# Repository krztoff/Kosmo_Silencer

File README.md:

# Kosmo_Silencer
Kosmo adaptation of the Befaco DivKid Mutes module

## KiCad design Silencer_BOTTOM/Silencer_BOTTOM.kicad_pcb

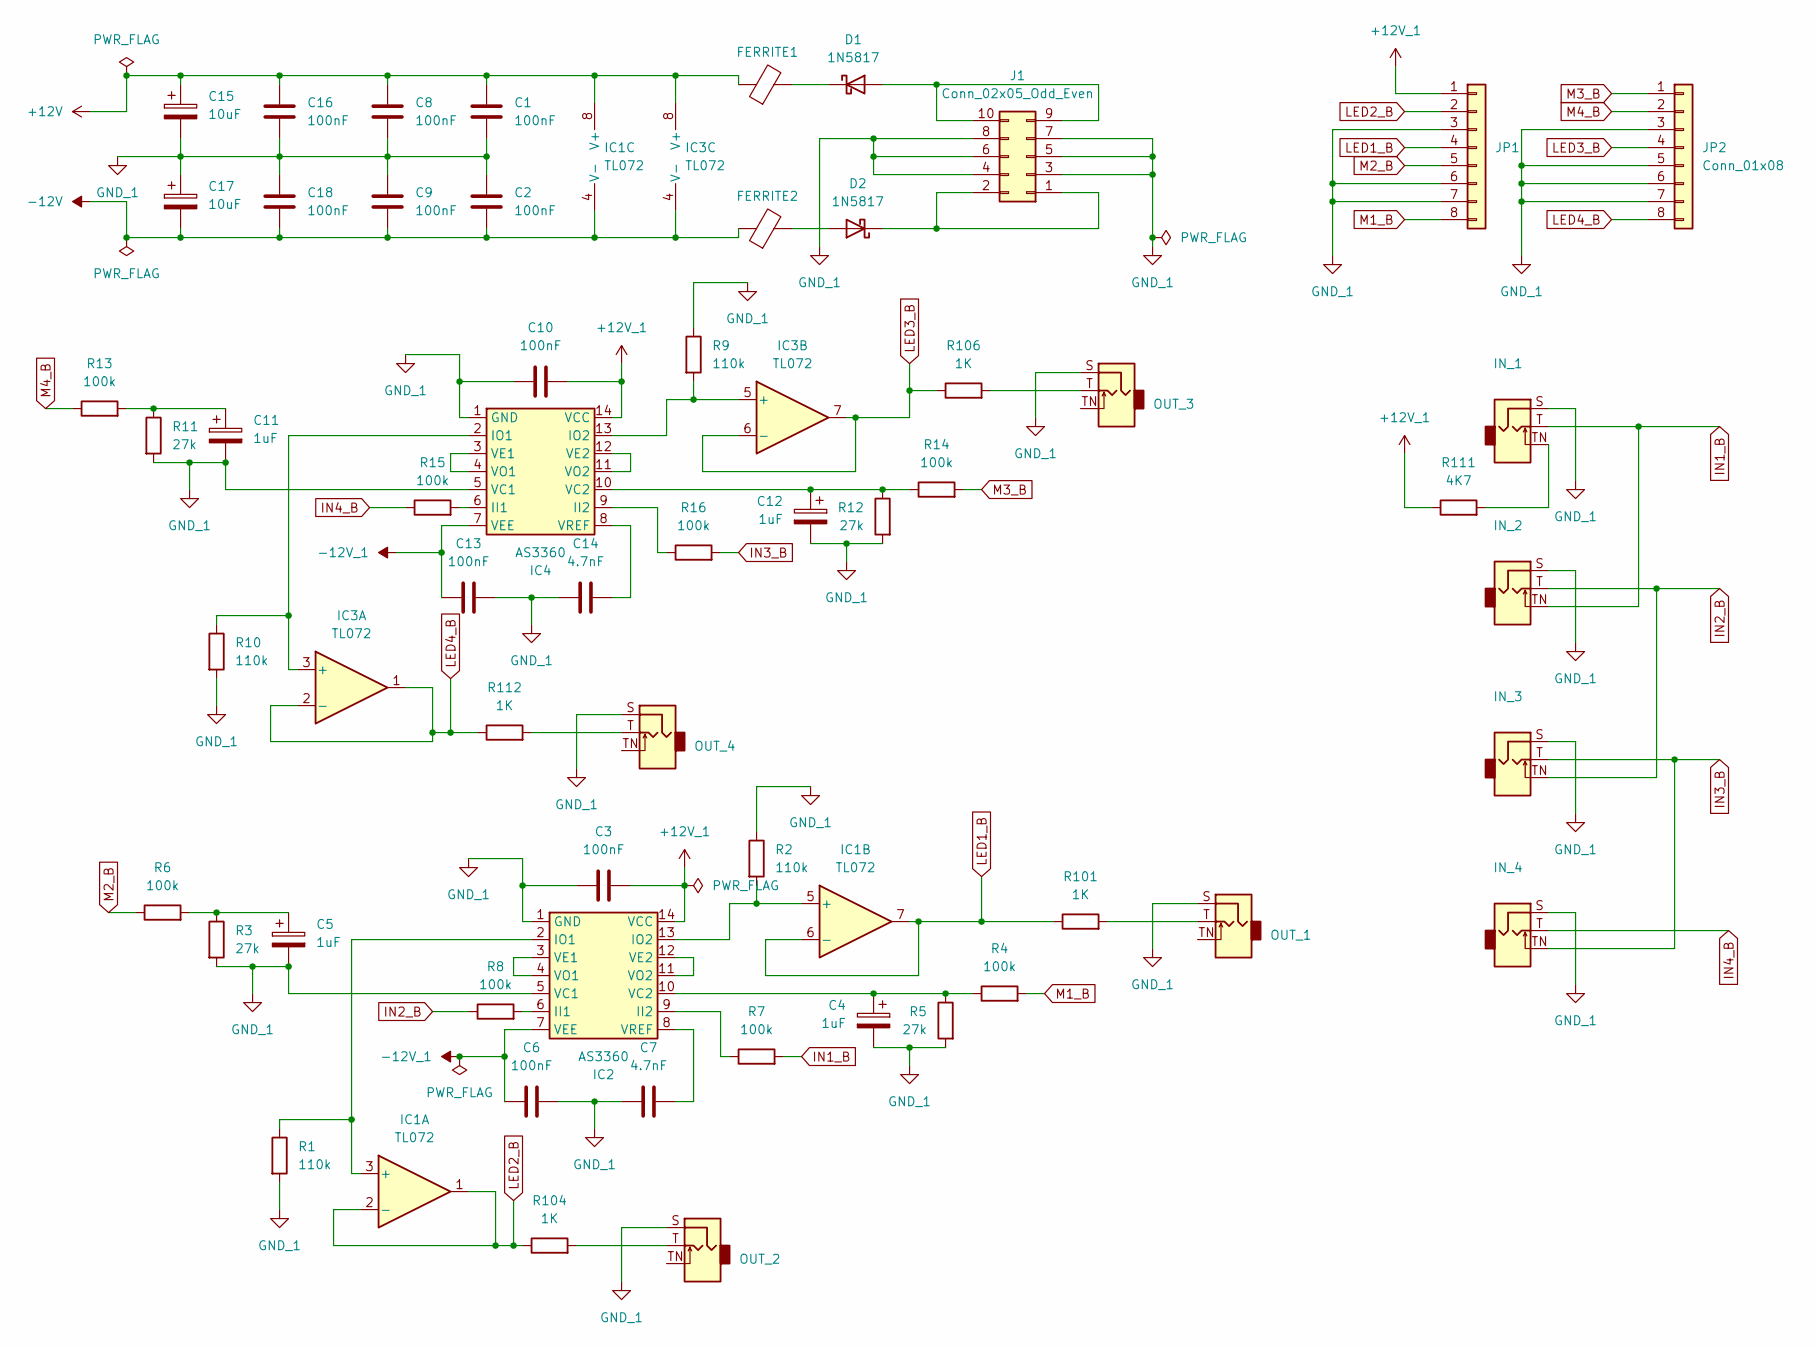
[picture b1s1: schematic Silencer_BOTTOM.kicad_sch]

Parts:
C1, C2, C3, C6, C8, C9, C10, C13, C16, C18: 100nF; C_Disc_D3.0mm_W2.0mm_P2.50mm
C4, C5, C11, C12: 1uF; CP_Radial_D6.3mm_P2.50mm
C7, C14: 4.7nF; C_Disc_D3.0mm_W2.0mm_P2.50mm
C15, C17: 10uF; CP_Radial_D6.3mm_P2.50mm
D1, D2: 1N5817; D_DO-41_SOD81_P10.16mm_Horizontal
FERRITE1, FERRITE2: FerriteBead; R_Axial_DIN0207_L6.3mm_D2.5mm_P10.16mm_Horizontal
IC1, IC3: TL072; DIP-8_W7.62mm_Socket_LongPads
IC2, IC4: AS3360; DIP-14_W7.62mm_LongPads
IN_1, IN_2, IN_3, IN_4: AudioJack2_SwitchT; Jack_6.35mm_PJ_629HAN_slots
J1: Conn_02x05_Odd_Even; Power_Header
JP1, JP2: Conn_01x08; PinHeader_1x08_P2.54mm_Vertical
OUT_1, OUT_2, OUT_3, OUT_4: AudioJack2_SwitchT; Jack_6.35mm_PJ_629HAN_slots
R1, R2, R9, R10: 110k; R_Axial_DIN0207_L6.3mm_D2.5mm_P10.16mm_Horizontal
R3, R5, R11, R12: 27k; R_Axial_DIN0207_L6.3mm_D2.5mm_P10.16mm_Horizontal
R4, R6, R7, R8, R13, R14, R15, R16: 100k; R_Axial_DIN0207_L6.3mm_D2.5mm_P10.16mm_Horizontal
R101, R104, R106, R112: 1K; R_Axial_DIN0207_L6.3mm_D2.5mm_P10.16mm_Horizontal
R111: 4K7; R_Axial_DIN0207_L6.3mm_D2.5mm_P10.16mm_Horizontal

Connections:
+12V: C1.1, C8.1, C15.1, C16.1, FERRITE1.1, IC1.8 (V+), IC3.8 (V+)
+12V_1: C3.2, C10.2, IC2.14 (VCC), IC4.14 (VCC), JP1.1, R111.1
-12V: C2.2, C9.2, C17.2, C18.2, FERRITE2.1, IC1.4 (V-), IC3.4 (V-)
-12V_1: C6.1, C13.1, IC2.7 (VEE), IC4.7 (VEE)
GND_1: C1.2, C2.1, C3.1, C4.2, C5.2, C6.2, C7.1, C8.2, C9.1, C10.1, C11.2, C12.2, C13.2, C14.1, C15.2, C16.2, C17.1, C18.1, IC2.1 (GND), IC2.5 (VC1), IC4.1 (GND), IC4.5 (VC1), IN_1.S, IN_2.S, IN_3.S, IN_4.S, J1.3, J1.4, J1.5, J1.6, J1.7, J1.8, JP1.3, JP1.6, JP1.7, JP2.3, JP2.5, JP2.6, JP2.7, OUT_1.S, OUT_2.S, OUT_3.S, OUT_4.S, R1.2, R2.1, R3.2, R5.2, R9.1, R10.2, R11.2, R12.2
IN1_B: IN_1.T, IN_2.TN, R7.2
IN2_B: IN_2.T, IN_3.TN, R8.1
IN3_B: IN_3.T, IN_4.TN, R16.2
IN4_B: IN_4.T, R15.1
LED1_B: IC1.6 (-), IC1.7, JP1.4, R101.1
LED2_B: IC1.1, IC1.2 (-), JP1.2, R104.1
LED3_B: IC3.6 (-), IC3.7, JP2.4, R106.1
LED4_B: IC3.1, IC3.2 (-), JP2.8, R112.1
M1_B: JP1.8, R4.2
M2_B: JP1.5, R6.1
M3_B: JP2.1, R14.2
M4_B: JP2.2, R13.1
unnamed: C5.1, R3.1, R6.2
unnamed: C11.1, R11.1, R13.2
unnamed: D1.2 (A), J1.9, J1.10
unnamed: D1.1 (K), FERRITE1.2
unnamed: D2.2 (A), FERRITE2.2
unnamed: D2.1 (K), J1.1, J1.2
unnamed: IC1.3 (+), IC2.2 (IO1), R1.1
unnamed: IC1.5 (+), IC2.13 (IO2), R2.2
unnamed: IC2.6 (II1), R8.2
unnamed: IC2.9 (II2), R7.1
unnamed: C4.1, IC2.10 (VC2), R4.1, R5.1
unnamed: IC2.3 (VE1), IC2.4 (VO1)
unnamed: IC2.11 (VO2), IC2.12 (VE2)
unnamed: C7.2, IC2.8 (VREF)
unnamed: IC3.3 (+), IC4.2 (IO1), R10.1
unnamed: IC3.5 (+), IC4.13 (IO2), R9.2
unnamed: IC4.6 (II1), R15.2
unnamed: IC4.9 (II2), R16.1
unnamed: C12.1, IC4.10 (VC2), R12.1, R14.1
unnamed: IC4.3 (VE1), IC4.4 (VO1)
unnamed: IC4.11 (VO2), IC4.12 (VE2)
unnamed: C14.2, IC4.8 (VREF)
unnamed: IN_1.TN, R111.2
unnamed: OUT_1.T, R101.2
unnamed: OUT_2.T, R104.2
unnamed: OUT_3.T, R106.2
unnamed: OUT_4.T, R112.2

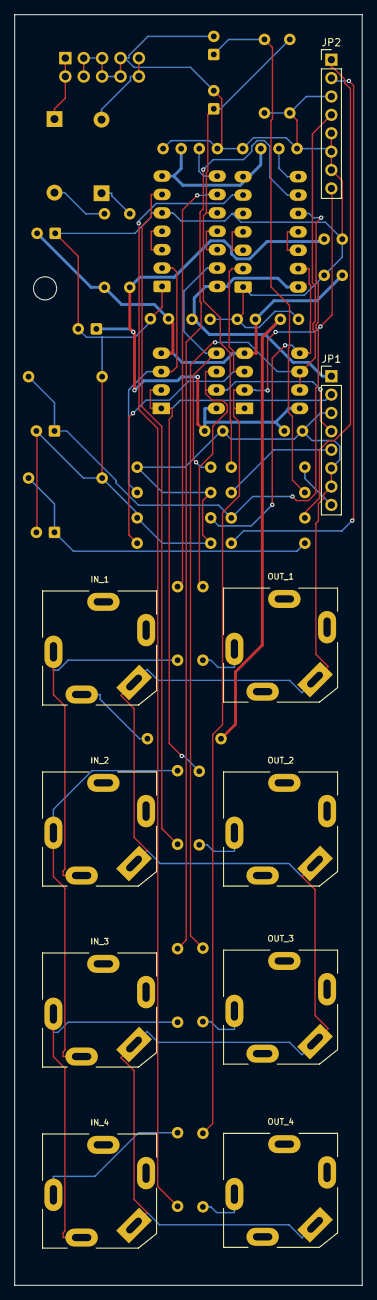
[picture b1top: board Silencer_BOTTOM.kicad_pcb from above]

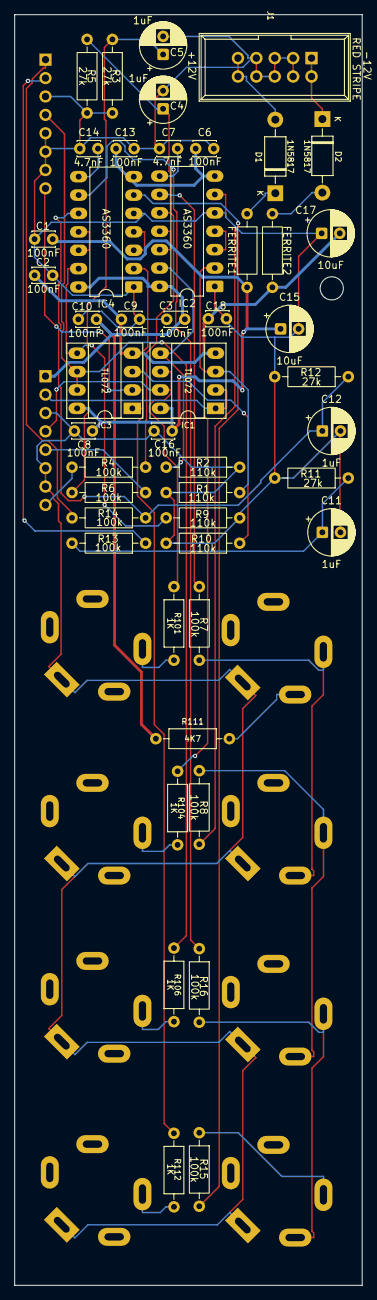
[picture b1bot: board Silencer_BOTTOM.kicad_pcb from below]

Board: 2 copper layers, 48.0 x 175.5 mm, 58 parts (48 on the bottom side), 44 nets.

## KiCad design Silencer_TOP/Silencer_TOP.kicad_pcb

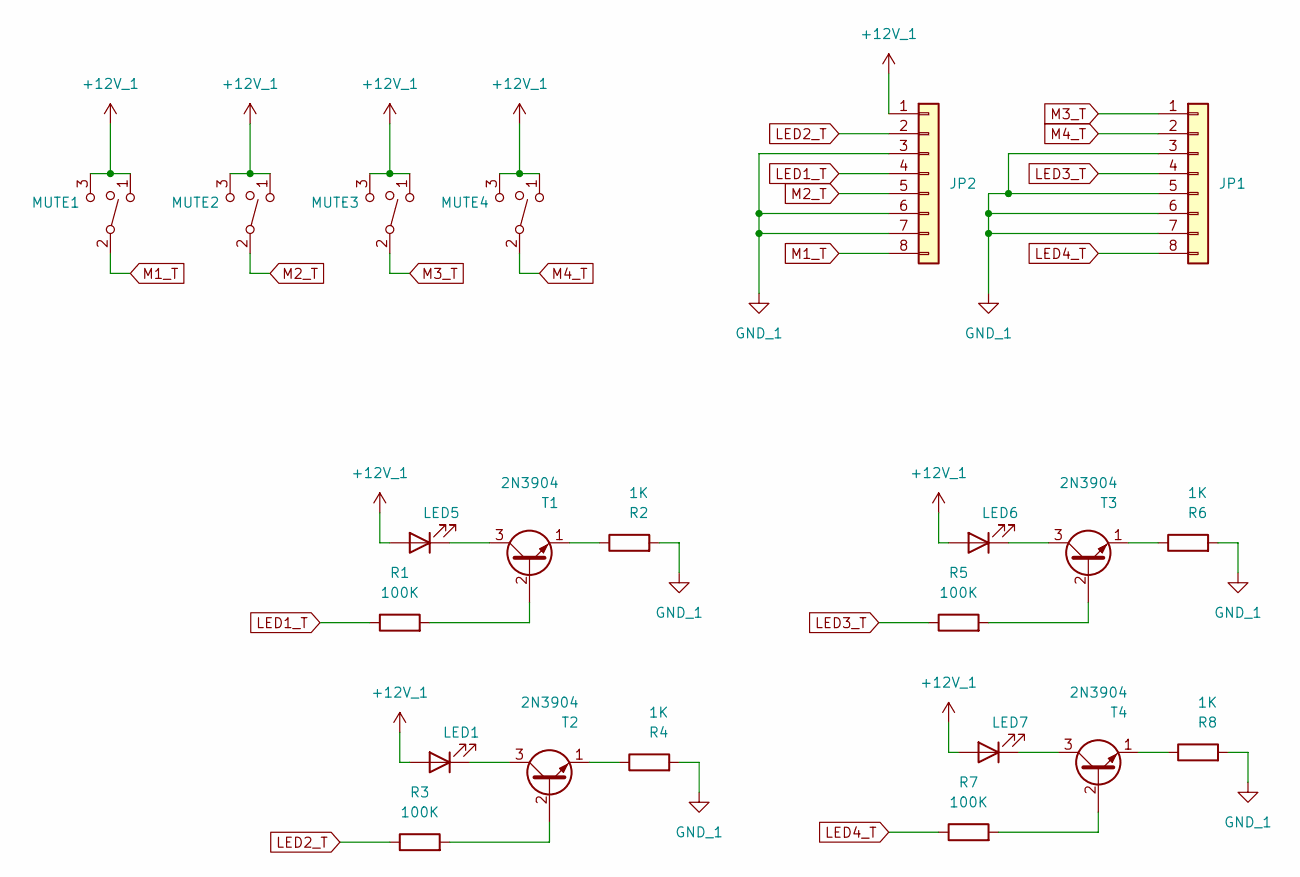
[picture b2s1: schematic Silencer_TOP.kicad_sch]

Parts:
JP1, JP2: Conn_01x08_MountingPin; PinHeader_1x08_P2.54mm_Vertical
LED1, LED5, LED6, LED7: LED_red; LED_D5.0mm
MUTE1, MUTE2, MUTE3, MUTE4: SW_SPDT_MSM; SPDT-toggle-switch-1M-series
R1, R3, R5, R7: 100K; R_Axial_DIN0207_L6.3mm_D2.5mm_P10.16mm_Horizontal
R2, R4, R6, R8: 1K; R_Axial_DIN0207_L6.3mm_D2.5mm_P10.16mm_Horizontal
T1, T2, T3, T4: 2N3904; TO-92_Inline_Wide

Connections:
+12V_1: JP2.1, LED1.2 (A), LED5.2 (A), LED6.2 (A), LED7.2 (A), MUTE1.1, MUTE1.3, MUTE2.1, MUTE2.3, MUTE3.1, MUTE3.3, MUTE4.1, MUTE4.3
GND_1: JP1.3, JP1.5, JP1.6, JP1.7, JP2.3, JP2.6, JP2.7, R2.2, R4.2, R6.2, R8.2
LED1_T: JP2.4, R1.1
LED2_T: JP2.2, R3.1
LED3_T: JP1.4, R5.1
LED4_T: JP1.8, R7.1
M1_T: JP2.8, MUTE1.2
M2_T: JP2.5, MUTE2.2
M3_T: JP1.1, MUTE3.2
M4_T: JP1.2, MUTE4.2
unnamed: LED1.1 (K), T2.3 (C)
unnamed: LED5.1 (K), T1.3 (C)
unnamed: LED6.1 (K), T3.3 (C)
unnamed: LED7.1 (K), T4.3 (C)
unnamed: R1.2, T1.2 (B)
unnamed: R2.1, T1.1 (E)
unnamed: R3.2, T2.2 (B)
unnamed: R4.1, T2.1 (E)
unnamed: R5.2, T3.2 (B)
unnamed: R6.1, T3.1 (E)
unnamed: R7.2, T4.2 (B)
unnamed: R8.1, T4.1 (E)

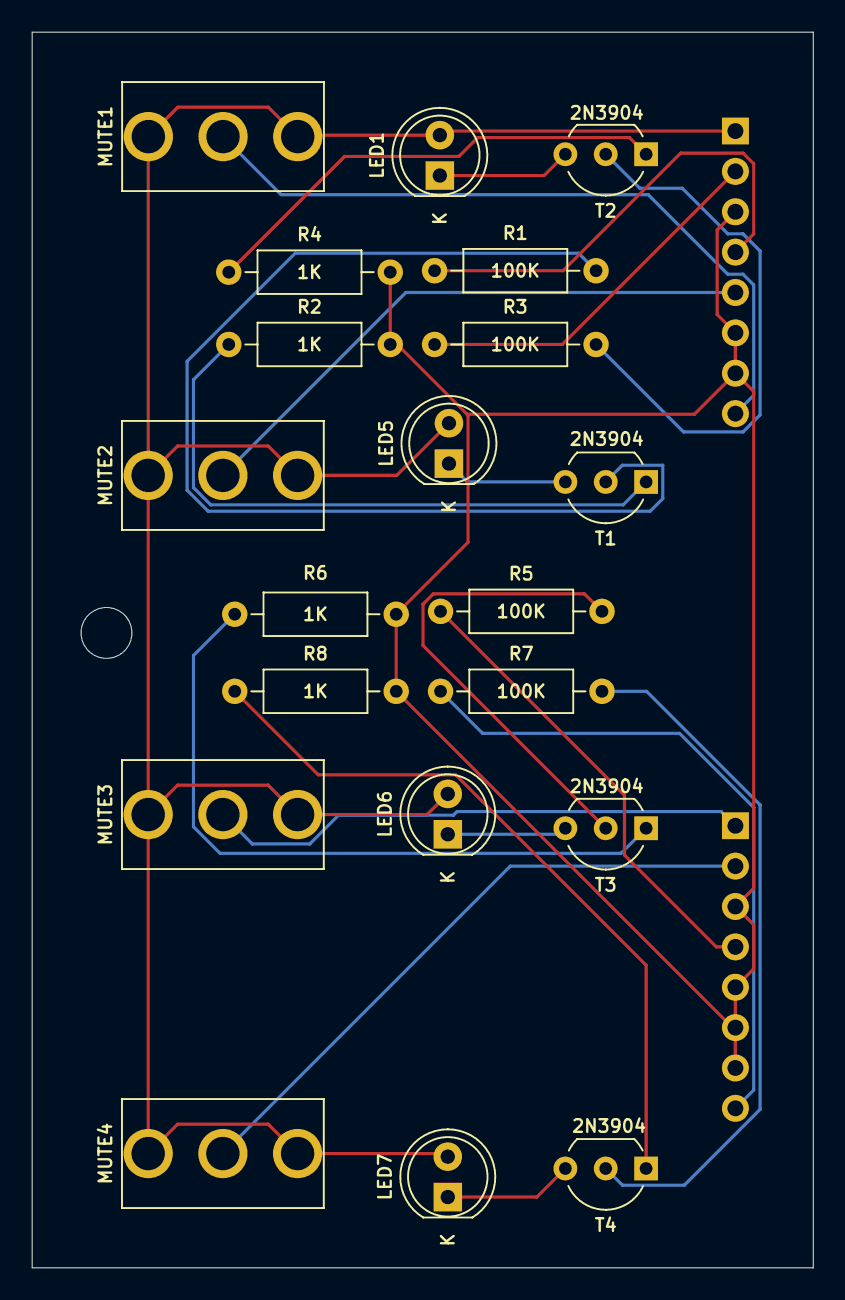
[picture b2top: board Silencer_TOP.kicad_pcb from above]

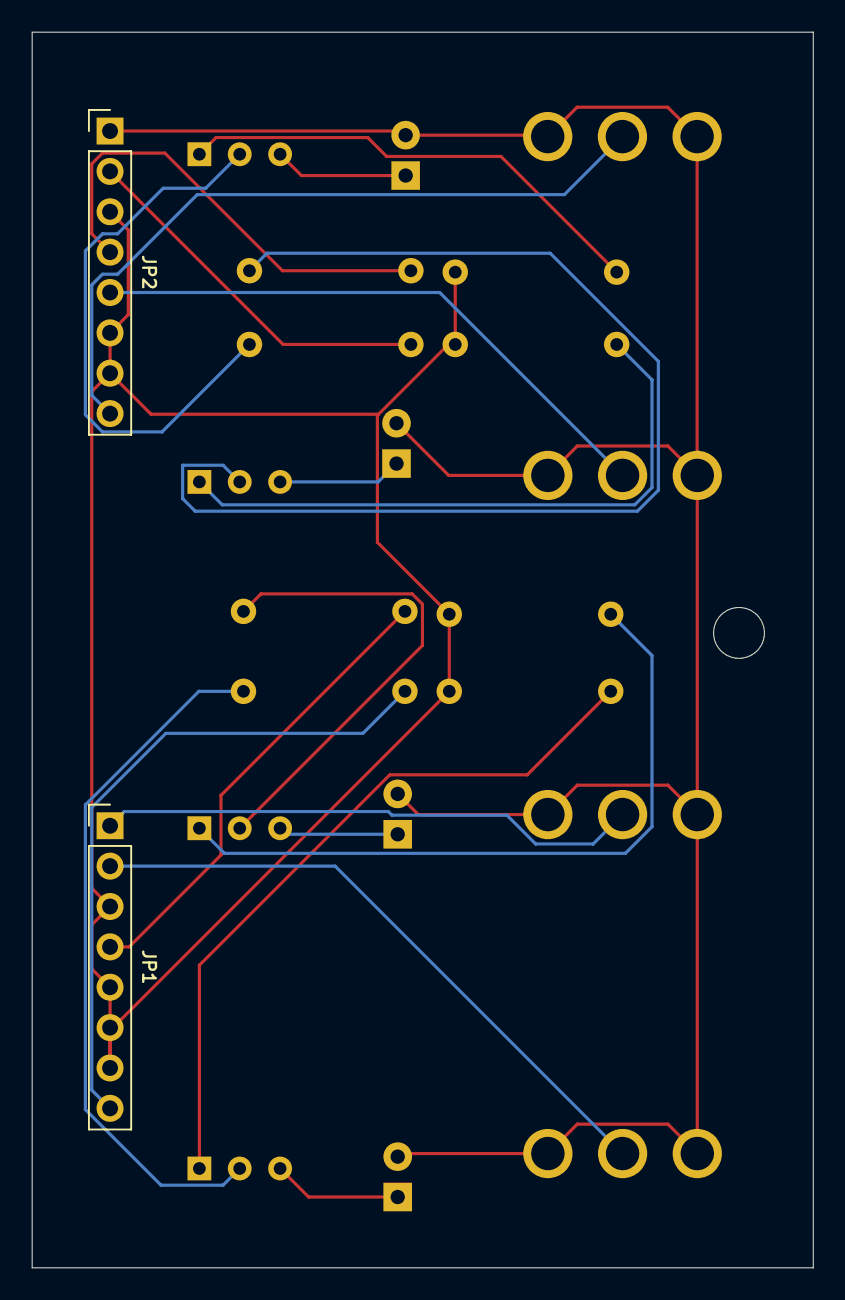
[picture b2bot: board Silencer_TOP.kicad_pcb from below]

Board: 2 copper layers, 49.1 x 77.8 mm, 22 parts (2 on the bottom side), 22 nets.

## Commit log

2025-07-10 Add PWR_FLAG to nets
2025-07-12 Panel layout and artwork (near?) complete.
2025-07-12 Moved "silencer" text to copper layer
2025-07-12 close project
2025-07-12 add grave shade font to panel folder
2025-07-12 add silencer font to repo
2025-07-12 Top board initial placement.
2025-07-19 Refactor Top and Bottom Schematics.
    Had to move input/output jacks to bottom board. This required a full refactoring of both and will mean re-doing the pcb layout of the top board.
2025-07-20 Top Board Layout lined up and routed.
2025-07-21 Bottom board layout roughed out. Routing began
2025-07-21 Routed and silkscreen cleaned up
2025-07-21 Routing Complete?
